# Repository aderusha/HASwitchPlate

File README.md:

# We're Moving!

This repository is an archived snapshot of the pre-1.0 HASP project.

## [Click here to head to the new home for HASPone!](https://github.com/HASwitchPlate/HASPone)

Below you'll find saved information about previous versions of HASP.

---

# HA SwitchPlate

The HA SwitchPlate is a user-programmable LCD touchscreen you can mount into a [standard North American work box](https://www.nema.org/Standards/ComplimentaryDocuments/NEMA%20WD%206%20-%20Dimensions%20for%20Wiring%20Devices%20-%20Excerpt.pdf) in place of a light switch.  It connects to your home automation system over WiFi to send and receive [MQTT](https://en.wikipedia.org/wiki/MQTT) messages in response to user interactions on the screen or events happening in your home.  The result is an attractive and highly-customizable controller for your home automation system which you can build yourself!

The HA SwitchPlate ("HASP") utilizes a [Nextion 2.4" LCD Touchscreen display](https://amzn.to/2TRTEU2) mounted in a 3D-printed enclosure as a touchscreen panel for home control and information display.  An [ESP8266-based microcontroller](https://amzn.to/2UZlga4) provides WiFi connectivity and system control.  The project has been developed to integrate with [Home Assistant](https://home-assistant.io/) and [OpenHAB](https://www.openhab.org/) but [should be compatible](Documentation/06_MQTT_Control.md) with any other MQTT-enabled automation platform such as [Domoticz](https://www.domoticz.com/wiki/MQTT), [Node-Red](http://noderedguide.com/tag/mqtt/), [Wink](https://github.com/danielolson13/wink-mqtt), [SmartThings](https://github.com/stjohnjohnson/smartthings-mqtt-bridge), [Vera](https://github.com/jonferreira/vera-mqtt), [HomeKit](https://www.npmjs.com/package/homekit2mqtt), etc.

The [Arduino code](Arduino_Sketch) for the ESP8266 provides a generic gateway between [MQTT](https://en.wikipedia.org/wiki/MQTT) and the [Nextion instruction set](https://www.itead.cc/wiki/Nextion_Instruction_Set).  A basic [Nextion HMI display file](Nextion_HMI) has been included with several pages of various layouts to provide user controls or to present information in response to MQTT messages sent to the device.

## Demo screens

## Purchase an assembled unit

As this build requires some specialist skills and tools, I will occasionally be [offering assembled devices for sale here](https://www.tindie.com/products/luma/ha-switchplate-hasp-single-wide-assembled/).

## Buy me a coffee

This project is powered by coffee.  [I might get a little weird about it at times](https://github.com/aderusha/RoastLearner), but it's not much of a stretch to suggest that coffee both powers and consumes a fair portion of my mental energy.  [Hook me up if you think HASP is cool](https://www.buymeacoffee.com/gW5rPpsKR).  Thanks!

## Bill of Materials

To build a simple version of this project you will minimally need the [Nextion display](https://amzn.to/2DIpahB) and the [WeMos D1 Mini](https://amzn.to/2Gc92Xs), 4 jumper wires, and a USB cable to power both devices.

A complete build that's ready to install will require the following components:

* [Nextion 2.4" LCD Touchscreen display](https://amzn.to/2RksiXr)
* [WeMos D1 Mini ESP8266 WiFi microcontroller](https://amzn.to/2UZlga4)
* [3D printed switch plate](3D_Printable_Models/HASwitchPlate_front_single.stl)
* [3D printed rear cover](3D_Printable_Models/HASwitchPlate_rear_nolcdmod.stl)
* [Mean Well IRM-03-5 AC to 5VDC Power supply](https://amzn.to/2UUWGa8)
* [PCB](PCB/)
* [2N3904 NPN Transistor](https://amzn.to/2TRuwwD)
* [1k Ohm Resistor](https://amzn.to/2Ec3kTZ)
* [4pin 2.54mm JST-XH PCB header](https://amzn.to/2Eaywmt)
* [Rubber grommet](https://amzn.to/2N6Etny)
* [6" each of white and black 300V 18AWG stranded power cables](https://amzn.to/2EcMmoA)
* [Two M2 self-tapping 6MM screws](https://amzn.to/2V0djBg) (or just any 4-6mm M2 screws) to mount PCB in rear enclosure
* [Four 20mm M2 flathead screws](https://amzn.to/2TQvd9N) and [four 3mm M2 threaded inserts](https://amzn.to/2N511Fh) to fasten both halves of the enclosure together

## Get Started!

[Check out the documentation](Documentation/) to get started building your own HA SwitchPlate.

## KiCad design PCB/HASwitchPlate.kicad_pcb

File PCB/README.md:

# We're Moving!

This repository is an archived snapshot of the pre-1.0 HASP project.

## [Click here to head to the new home for HASPone!](https://github.com/HASwitchPlate/HASPone)

Below you'll find saved information about previous versions of HASP.

---

# PCB source files and Gerber outputs

Above you'll find [KiCad](http://kicad-pcb.org/) [schematic](https://github.com/aderusha/HASwitchPlate/blob/master/PCB/HASwitchPlate.sch) and [PCB](https://github.com/aderusha/HASwitchPlate/blob/master/PCB/HASwitchPlate.kicad_pcb) files along with [a ZIP bundle containing complete gerber outputs](https://github.com/aderusha/HASwitchPlate/raw/master/PCB/HASwitchPlate.gerbers.zip) ready to send to [your favorite PCB shop](https://www.allpcb.com/?Mb_InviteId=34099).

I had these manufactured by [AllPCB](https://www.allpcb.com/?Mb_InviteId=34099) and I'm very happy with the results.  The quality has been perfect and their shipping time to the US has been under a week across several orders.  [If you sign up through this link](https://www.allpcb.com/?Mb_InviteId=34099)  they credit me some cash that I can use for future projects which helps me out a bit.

If you aren't looking to buy a zillion boards, I may have some ready for US orders in [my Tindie store](https://www.tindie.com/products/luma/ha-switchplate-hasp-pcb/).

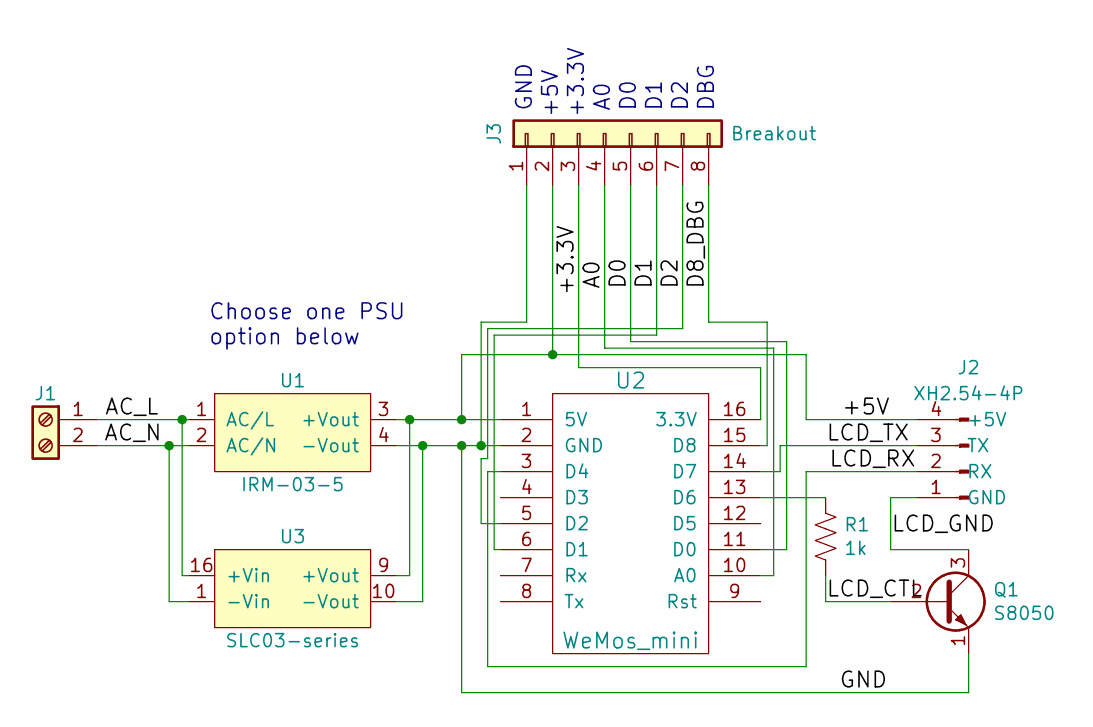
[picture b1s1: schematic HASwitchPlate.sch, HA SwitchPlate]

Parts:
J1: Screw Term.; TerminalBlock_bornier-2_P5.08mm
J2: XH2.54-4P; JST_XH2.54_04x2.54mm_Straight
J3: Breakout; Pin_Header_Straight_1x08_Pitch2.54mm
Q1: S8050; TO-92L_HandSolder
R1: 1k; R_Axial_DIN0207_L6.3mm_D2.5mm_P7.62mm_Horizontal
U1: IRM-03-5; ACDC-Converter_MeanWell-IRM-03-x
U2: WeMos_mini; wemos-d1-mini-with-pin-header-and-connector
U3: SLC03-series; ACDC-Converter_MeanWell-SLC03-series

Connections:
/+3.3V: J3.3, U2.16 (3.3V)
/+5V: J2.4 (+5V), J3.2, U1.3 (+Vout), U2.1 (5V), U3.9 (+Vout)
/A0: J3.4, U2.10 (A0)
/AC_L: J1.1, U1.1 (AC/L), U3.16 (+Vin)
/AC_N: J1.2, U1.2 (AC/N), U3.1 (-Vin)
/D0: J3.5, U2.11 (D0)
/D1: J3.6, U2.6 (D1)
/D2: J3.7, U2.5 (D2)
/D8_DBG: J3.8, U2.15 (D8)
/GND: J3.1, Q1.1 (E), U1.4 (-Vout), U2.2 (GND), U3.10 (-Vout)
/LCD_CTL: Q1.2 (B), R1.2
/LCD_GND: J2.1 (GND), Q1.3 (C)
/LCD_RX: J2.2 (RX), U2.3 (D4)
/LCD_TX: J2.3 (TX), U2.14 (D7)
unnamed: R1.1, U2.13 (D6)

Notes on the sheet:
GND
+5V
+3.3V
DBG
Choose one PSU option below

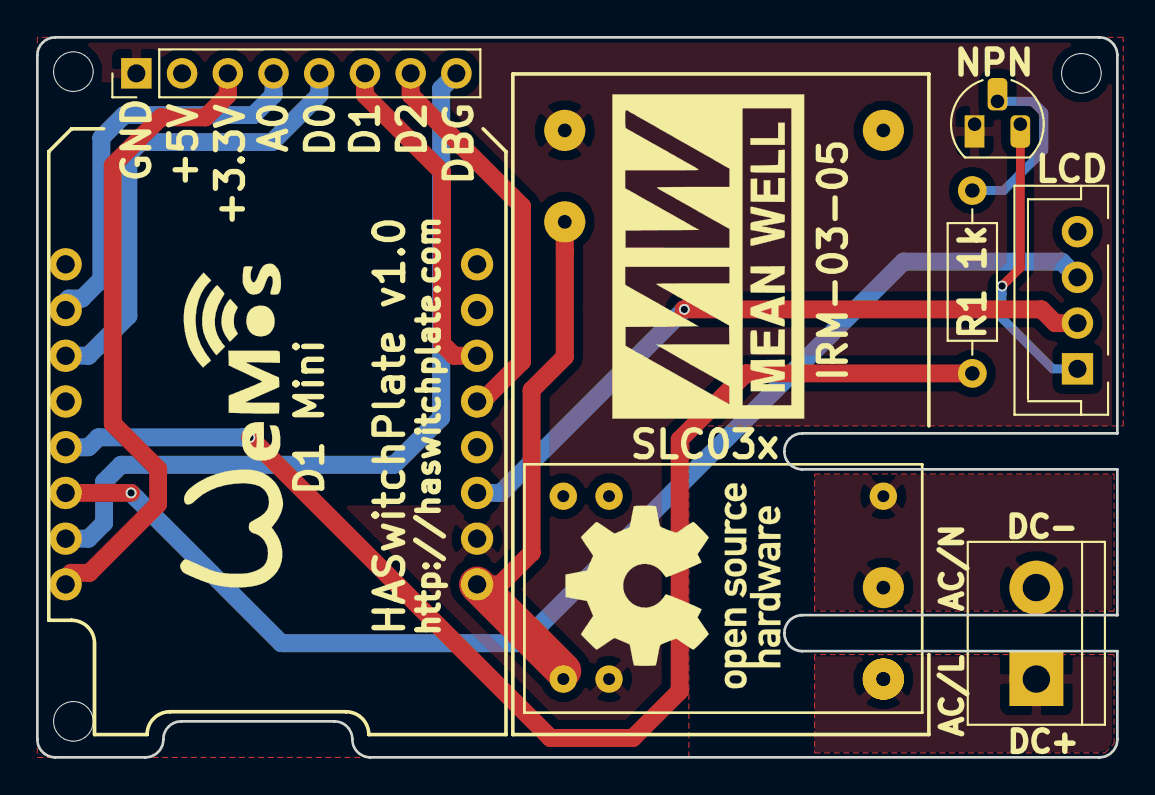
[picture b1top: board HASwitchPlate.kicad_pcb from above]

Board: 2 copper layers, 60.0 x 40.0 mm, 8 parts (0 on the bottom side), 15 nets.

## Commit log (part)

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2018-04-27 Update package for distribution
2018-04-27 Add gzipped package templates
2018-04-27 New HASP device deployment script
2018-04-27 Enhanced deployment script and documentation
2018-04-27 Deploy script
2018-04-28 deployhasp.sh without prename
2018-04-28 Home Assistant deployment documentation and updates
2018-04-28 Arduino sketch v0.2.3 release
2018-04-28 Update package
2018-04-30 Dcoumentation
2018-04-30 Add NodeMCU Flasher instructions
2018-04-30 Fix documentation anchors
2018-04-30 Documentation
2018-05-01 Add example configurations
2018-05-02 Version 0.24
2018-05-03 Change update URL to allow for future backend changes
2018-05-05 New enclosure design
2018-05-06 Nextion LCD modification
2018-05-06 Nextion LCD image
2018-05-06 Add part images
2018-05-06 Nextion simulator documentation
2018-05-06 Documentation fixes
2018-05-06 Add auto-update version file
2018-05-06 Change JSON format
2018-05-06 HASP version 0.26
2018-05-07 Correct 3D print model image
2018-05-07 Dcoumentation fixes
2018-05-10 Correction to Nextion trademarks
2018-05-11 Disable auto-update at 3am
2018-05-26 Bugfixes
2018-05-26 HASP v0.28
2018-05-27 Documentation updates
2018-05-28 Add triple-wide decora plate
2018-05-28 Add exploded model STL
2018-05-28 Hass.io installation documentation
2018-05-28 Add support for running it in any dir.
    1: Check if configuration.yaml is present i current dir.
    2: if not, search for that dir
    3: if 1 dir found, cd to that.
    4: if more that 1 dir, exit.
2018-05-29 Hass.io compatibility
2018-05-29 Package updates
2018-05-29 Hass.io compatibility fixes
2018-05-29 Fix clock at 12:00
2018-05-29 Cross-platform clock automation
2018-05-29 Add recorder domains
2018-05-31 Deployment updates
2018-06-01 HASP v0.29
2018-06-04 UK face plate for testing
2018-06-10 Revert SketchUp model to 2017
2018-07-02 Add 5x decora plate for @jpe-nyc
2018-08-09 Documentation update
2018-08-22 Simplify HA automations for adjusting font/font size by implementing a couple of scripts
2018-08-26 Implement HASP support for subscribing to group commands
2018-08-26 Update documentation to explain the group name subscriptions and group-lev commands
2018-09-08 Create a new python script for updating foreground/background colors at once
2018-09-18 typos
2018-09-18 Fix for hang when DHCP not available
2018-09-18 Revert script calls
2018-10-15 HASP 0.30
2018-10-15 Revert demo screenshots
2018-12-03 Model updates for easier printing
2018-12-05 deployhasp.sh fixes for embedded broker
2018-12-05 Home Assistant documentation updates
2018-12-05 HASP 0.31
2018-12-05 HASP v0.31
2018-12-11 Add MQTT return code reference
2018-12-11 Add Nextion color code information
2018-12-12 Add note regarding Enhanced displays
2018-12-12 Update Nextion instructions
2018-12-12 Add user contributed content
2018-12-12 Added openHAB items/rules/sitemap entries, to adapt the HASP for use with that home automation system. Also, created a Readme for easy installation/configuration.
2018-12-15 deployhasp.sh fix for recorder component
2018-12-20 Additional User Contributed 3D Printable Models
    HASwitchPlate_double_spacer.stl - 5mm spacer between front switchplate and wall.
    HASwitchPlate_front_double_blank.stl - Left HASP module and right is a blank for two gang boxes
    HASwitchPlate_front_nolcd.stl - Solid front plate to separate LCD from D1/Power
    HASwitchPlate_contrib - Source files for above
2018-12-22 Add limited TJC panel support
2018-12-31 Add HTML validation on `nodeName` field
2018-12-31 Sketchup export to 2017
2019-01-01 Minor 3D model updates and cleanup
2019-01-02 HASP version 0.33
2019-01-03 HASP v0.33
2019-01-03 Update electronics assembly documentation
2019-01-04 PCB v0.06
2019-01-04 Fix library table for portability
2019-01-04 Fix file paths for PCB publication
2019-01-05 MQTT documentation
2019-01-05 Nextion and MQTT documentation updates
2019-01-05 Nextion and MQTT documentation
2019-01-05 Nextion documentation update
2019-01-05 Nextion documentation
2019-01-06 Add minimum clearance rear enclosure
2019-01-06 Enclosure documentation update
2019-01-08 Fix alarm panel automations
2019-01-10 Fix weather automation for 0.85 breaking changes
2019-01-12 HASP v0.34
2019-01-14 Update packages package
2019-01-17 Fix TJC model name
2019-01-17 Fix Nextion model numbers
2019-01-21 2019/01/21(BK): Big updates to the code, including: -Works with multiple HASPs (two sample sets of files for Foyer/Master included) -Added Status screen automation example (indoor/outdoor temp, day &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
2019-01-22 BOM update
2019-01-22 BOM updates
2019-01-24 Initial changes to allow Hass 0.86+ to work
2019-01-30 Add docs
2019-01-30 Set theme jekyll-theme-minimal
2019-01-30 Clear out docs folder for github pages
2019-01-30 Set theme jekyll-theme-slate
2019-01-30 Create CNAME
2019-01-30 Update CNAME
2019-01-30 Update documentation
2019-02-08 HASP v0.36
2019-02-10 -Rewrote all openHAB->HASP rules to use the JSON command topic for formatting like button text and font size. -Removed all individual items for txt/font/bco topics (cut # of items down by half) -Adde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
2019-02-10 Added /state/JSON MQTT subtopic, which publishes all button and dimmer events, with values (ON/OFF for buttons, ON/val for dimmers) in JSON format. Resolves #52 in upstream
2019-02-10 Fixed case for state JSON topic ("JSON"->"json")
2019-02-11 Removing "OFF" event for now (unable to distinguish between two quick OFF->ON->OFF state changes in openHAB, due to state not being locked in during rule execution (so quick button presses were being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
2019-02-11 Added 3rd (testing) HASP, for testing the json state topic improvements (fewer items).
2019-02-13 Finalized openHAB config changes with the improved JSON state topic (removed all unnecessary status items and rewrote rules to handle the JSON state payloads.
2019-02-16 Incorporated denominator's fix for plate refresh rule trigger (should work on all reconnects now)
2019-02-17 Rename desktop models
2019-02-17 Fix desktop model names
2019-02-18 docuemntation updates
2019-02-18 ESP for Arduino 2.5.0 compatibility updates
2019-02-18 Dedicated wifiClient class for MQTT, restore mDNS port 80 advertisement
2019-02-20 Nextion firmware update from HTTP download performance and reliability
2019-02-22 30s MQTT retry interval, address WiFi dropouts while MQTT disconnected
2019-02-22 Fix Nextion upload from browser
2019-02-22 Add LCD upload timeouts to reset in case something goes wrong
2019-02-22 Add LCD update web ui workflow
2019-02-23 Fix mDNS using LEA MDNSResponder
2019-02-23 HASP 0.37
2019-02-24 fixing case in upgrade automation
2019-03-02 Add note about ESP8266 for Arduino 2.5.0 requirement
2019-03-25 Update documentation for compiling in Arduino IDE
2019-06-07 Fix Typo
2019-06-07 Fix (Typo):
    Fixed same typo as before
2019-06-10 SoftwareSerial fix
2019-06-10 Re-enable mDNS as it seems to not break things anymore
2019-06-12 Extend MQTT JSON memory allocation, fix AllPCB link
2019-06-12 Fix MDI icons and JSON array nulls
2019-06-12 Default Page automation and example automations documentation
2019-06-12 Add build and update artifacts for release
2019-06-12 Fix hasppackages
2019-06-21 Fix PCB link
2019-07-12 Update HASwitchPlate.ino
    This pull request to to add a beep tone on screen press. This will help people to know that the button press was successful.
    I have also added a MQTT command to allow invalid code tried it will beep a pattern. (once I get Yet another alarm system to update his code to allow this.)
    Thanks
    Ben
2019-08-09 Faceplate for India created by @ceaswaran
    Downloaded from https://www.thingiverse.com/thing:3712046
2020-02-11 HASP v0.39
2020-02-11 show_header_toggle
    add show_header_toggle: false to cards
2020-02-12 Minor post-0.39 fixes
2020-02-12 Fix "status" sensor device
2020-02-12 Add examples to migrate-hasp-107
2020-02-12 Hass.io install documentation
2020-02-13 Fixes for beep code, disable WiFi sleep, update for WiFiManager constants
2020-02-13 Add link to lspaula's Nextion background repo
2020-02-13 Set retain=true when publishing status and sensor messages
2020-02-28 HASP v0.40 beta 001
2020-02-28 HASP v0.40 beta 002
2020-02-28 HASP v0.40 beta 003
2020-02-29 HASP v0.40 Beta Documentation and 3D model updates
2020-03-13 Update templates for modern state handling
2020-03-18 Minor hass package bugfixes
2020-03-23 Replace FontAwesome icons w/ Material Design
2020-03-23 Update ESP8266 code for new MD icons
2020-03-23 Nextion files for MD icons
2020-03-23 Revert to FontAwesome
2020-03-26 Add backlight controls
2020-03-29 Recompiled TJC binary
2020-03-29 Update lovelace instructions
2020-03-29 Update demo images
2020-03-29 Update demo screens
2020-03-29 Fix model image
2020-03-29 Update main page model image
2020-03-29 More adjustments to demo models
2020-03-29 Update demo model pictures
2020-03-29 Update demo model images
2020-03-30 Fix for deployhasp package URL
2020-03-30 Remove periodic state publish, normalize MQTT debug msgs
2020-03-31 Remove duplicate models
2020-03-31 FA Icon docs
2020-03-31 Fix link to zonko16's repo
2020-03-31 Font documentation
2020-04-07 Fix Nextion purchase link
2020-04-26 Correct m2 insert dimensions
2020-05-08 Deal with the newest batch of breaking changes
2020-05-10 fix hasp-examples path
2020-07-15 Add Inverted HMI
2020-08-22 extend the mqttUser/Pass fields to be 128 bytes long in all the places
2020-08-22 fix a typo? the html field for mqttServer is limited to 39 chars, but the buffer can take 63
2020-12-01 Documentation updates and new soldering jig model
2020-12-19 gitignore update
2020-12-19 Updated Home Assistant integration instructions
2020-12-19 Update packages to accomodate breaking changes
2020-12-19 deployhasp.sh fix for recorder, remove mqtt
2020-12-20 Add fonts + Lovelace to message display automation
2020-12-20 Remove group and add lovelace config
2020-12-20 Remove deprecated group entities
2020-12-20 Lovelace updates
2020-12-22 Enhanced LCD serial support
2020-12-23 Expanded Nextion return code reporting
2020-12-24 Testing with BearSSL
2020-12-26 Add version-insecure.json
    Add backward-compatible version file to allow update checks and updates from HASP versions prior to v0.41.
2020-12-26 Migrate version check to secure update links
2020-12-26 Enable TLS for MQTT and update checks
2020-12-26 Update version.json
    Fix github raw download links to avoid 302 redirect
2020-12-26 HASP LCD v3
2020-12-26 HASP update updated for updated updates
2020-12-26 TLS fixes for MQTT and FW updates
2020-12-27 Update compiled binary
2020-12-27 deck chairs re-arranged
2020-12-27 Potential startup race condition
2020-12-27 re-sequence first stage startup. again.
2020-12-27 Add MQTT TLS options to WiFiManager
2020-12-27 Attempt to address occasional SPIFFS crash on boot
2020-12-27 WiFiManager TLS fix
2021-01-06 dev work on hass package
2021-01-07 Initial work on GUI HASP device customization
2021-01-07 Updated dev deploy
2021-01-07 Retain MQTT backlight messages
2021-01-08 Better handling and reporting of backlight state
2021-01-09 Updates automations for pages 1 and 2
2021-01-09 Improved status tracking and reporting
2021-01-10 Pad EOF w/ LFs
2021-01-11 Add desktop minibase model
2021-01-20 testing hass automations
2021-01-20 Add lovelace files to deployhasp s+r
2021-01-24 Initial test blueprints
2021-01-25 MQTT discovery and JSON events
2021-01-25 Update blueprints
2021-01-29 Replace home assistant packages with blueprints
2021-01-29 HASP firmware v0.41 beta
2021-01-31 Retain page messages
2021-01-31 Fix JSON error in JSON error message
2021-02-02 blueprints!
2021-02-03 Normalize JSON action reports
2021-02-03 blueprint development
2021-02-03 monospace != proportional
2021-02-03 Fix icon overlay delay conditions
2021-02-03 Add Nextion buffer overrun backoff and retrans
2021-02-04 beta
2021-02-05 Enable nextion command confirmations
2021-02-05 Compiled ESP8266 code
2021-02-05 Nextion v3 beta
2021-02-05 Defer updateCheck
2021-02-05 blueprint fixes
2021-02-06 Remove connections from device discovery JSON
2021-02-07 Workardound for WiFi not connecting on first boot
2021-02-09 Increase JSON config mem alloc
2021-02-09 Increase JSON config mem
2021-02-13 re-work MQTT connect loop logic
2021-02-15 Improved handling and reporting of MQTT connect errors
2021-02-18 Change MQTT error reports + Nextion response timeout
2021-03-03 HASPone announcement
2021-03-03 Update to HASPone
2021-03-03 HASPone
2021-03-16 Point to new repo
